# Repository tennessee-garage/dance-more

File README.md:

# dance-more
The next generation of the dancefloor

To get the repo running on your own machine (no floor needed), start with
[docs/getting-started.md](docs/getting-started.md).

Design docs live in [docs/](docs/README.md). To write an animation for the floor, start with [docs/animations.md](docs/animations.md).

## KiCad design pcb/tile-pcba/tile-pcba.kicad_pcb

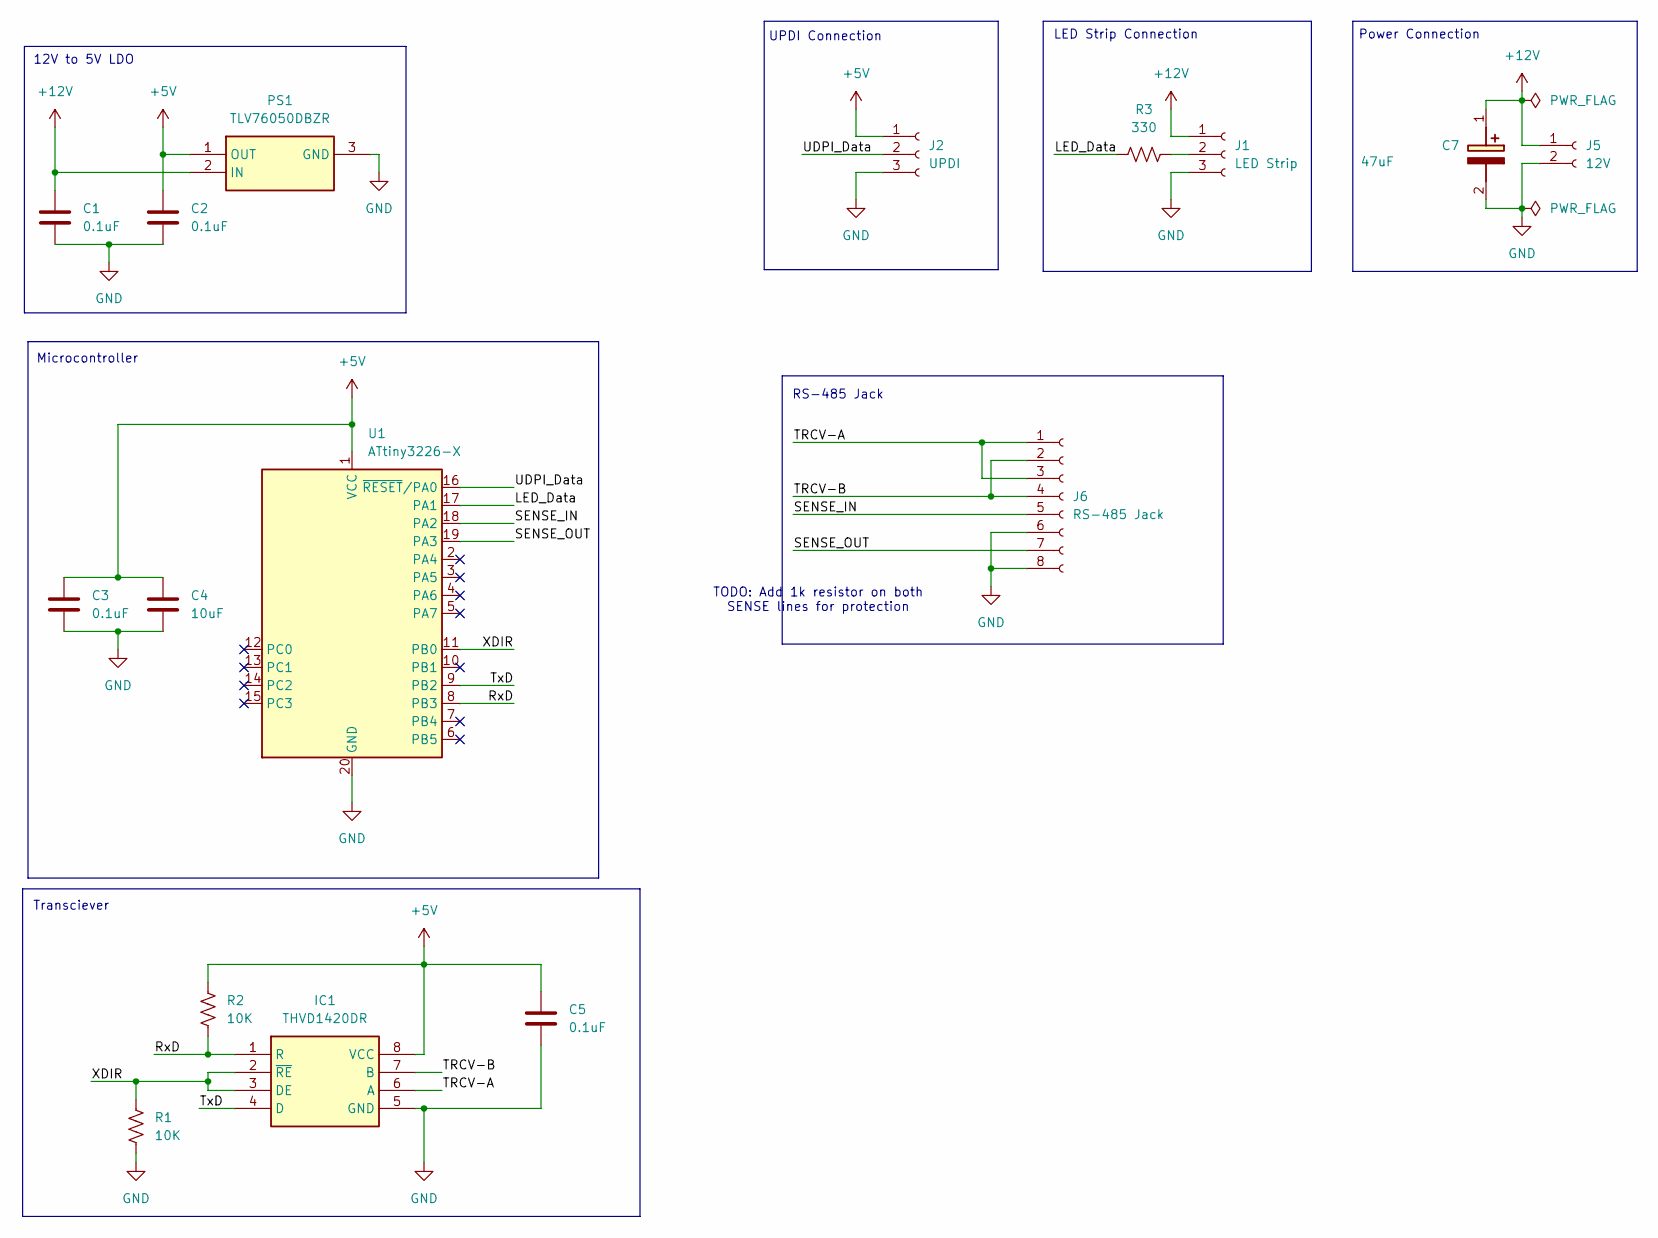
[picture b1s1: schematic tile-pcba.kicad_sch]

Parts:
C1, C2, C3, C5: 0.1uF; C_0805_2012Metric_Pad1.18x1.45mm_HandSolder; LCSC C49678
C4: 10uF; C_0805_2012Metric_Pad1.18x1.45mm_HandSolder; LCSC C1713
C7: 47uF; CAPAE530X550N; Mouser Part Number 710-865080342006
IC1: THVD1420DR; SOIC127P600X175-8N; Mouser Part Number 595-THVD1420DR
J1: LED Strip; PinHeader_1x03_P2.54mm_Vertical; LCSC C92159
J2: UPDI; PinHeader_1x03_P2.54mm_Vertical
J5: 12V; JST_XH_B2B-XH-A_1x02_P2.50mm_Vertical; LCSC C158012
J6: RS-485 Jack; 8P8C RA RJ45 Jack
PS1: TLV76050DBZR; SOT95P237X112-3N; Mouser Part Number 595-TLV76050DBZR
R1, R2: 10K; R_0805_2012Metric_Pad1.20x1.40mm_HandSolder; LCSC C17414
R3: 330; R_0805_2012Metric_Pad1.20x1.40mm_HandSolder; LCSC C17630
U1: ATtiny3226-X; SSOP-20_5.3x7.2mm_P0.65mm; Manufacturer Part Number ATTINY3226-XF; Mouser Part Number 579-ATTINY3226-XF

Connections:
+5V: C2.1, C3.1, C4.1, C5.1, IC1.8 (VCC), J2.1, PS1.1 (OUT), R2.1, U1.1 (VCC)
+12V: C1.1, C7.1 (+), J1.1, J5.1, PS1.2 (IN)
/LED_Data: R3.1, U1.17 (PA1)
/RxD: IC1.1 (R), R2.2, U1.8 (PB3)
/SENSE_IN: J6.5, U1.18 (PA2)
/SENSE_OUT: J6.7, U1.19 (PA3)
/TRCV-A: IC1.6 (A), J6.1, J6.3
/TRCV-B: IC1.7 (B), J6.2, J6.4
/TxD: IC1.4 (D), U1.9 (PB2)
/UDPI_Data: J2.2, U1.16 (~RESET/PA0)
/XDIR: IC1.2 (~RE), IC1.3 (DE), R1.1, U1.11 (PB0)
GND: C1.2, C2.2, C3.2, C4.2, C5.2, C7.2 (-), IC1.5 (GND), J1.3, J2.3, J5.2, J6.6, J6.8, PS1.3 (GND), R1.2, U1.20 (GND)
unnamed: J1.2, R3.2

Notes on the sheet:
TODO: Add 1k resistor on both SENSE lines for protection
UPDI Connection
LED Strip Connection
RS-485 Jack
Microcontroller
12V to 5V LDO
Transciever
Power Connection

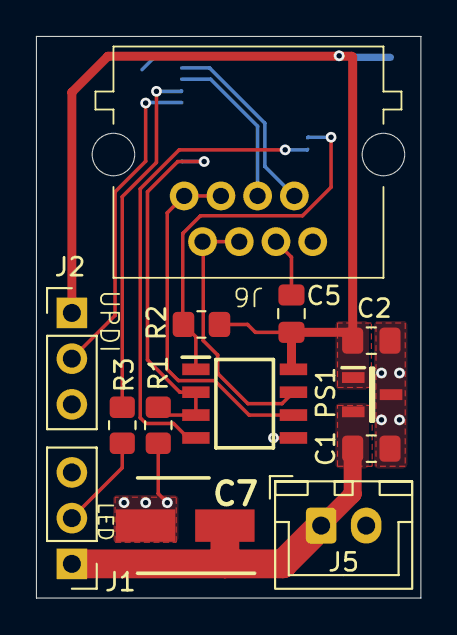
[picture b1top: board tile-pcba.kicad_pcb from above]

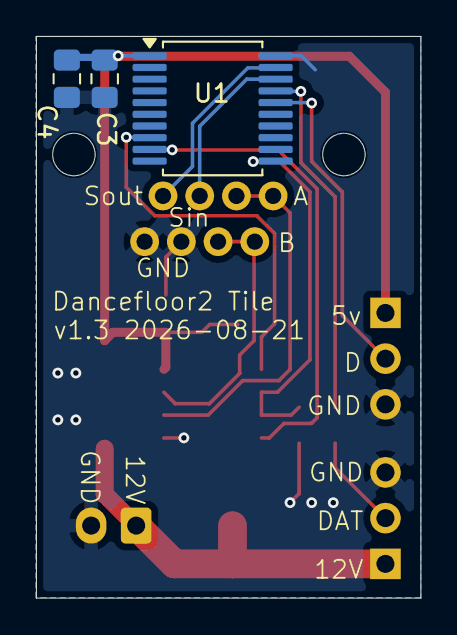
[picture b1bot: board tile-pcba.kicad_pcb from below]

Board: 2 copper layers, 21.4 x 31.2 mm, 16 parts (3 on the bottom side), 13 nets.

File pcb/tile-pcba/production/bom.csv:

Designator,Footprint,Quantity,Value,LCSC Part #
"C1, C2, C3, C5",0805,4,0.1uF,C49678
C4,0805,1,10uF,C1713
C7,CAPAE530X550N,1,47uF,C249915
IC1,SOIC127P600X175-8N,1,THVD1420DR,C3235215
J1,PinHeader_1x03_P2.54mm_Vertical,1,LED Strip,C92159
J2,PinHeader_1x03_P2.54mm_Vertical,1,UPDI,
J5,JST_XH_B2B-XH-A_1x02_P2.50mm_Vertical,1,12V,C158012
J6,8P8C RA RJ45 Jack,1,RS-485 Jack,
PS1,SOT95P237X112-3N,1,TLV76050DBZR,C2867465
"R1, R2",0805,2,10K,C17414
R3,0805,1,330,C17630
U1,SSOP-20_5.3x7.2mm_P0.65mm,1,ATtiny3226-X,C3235640

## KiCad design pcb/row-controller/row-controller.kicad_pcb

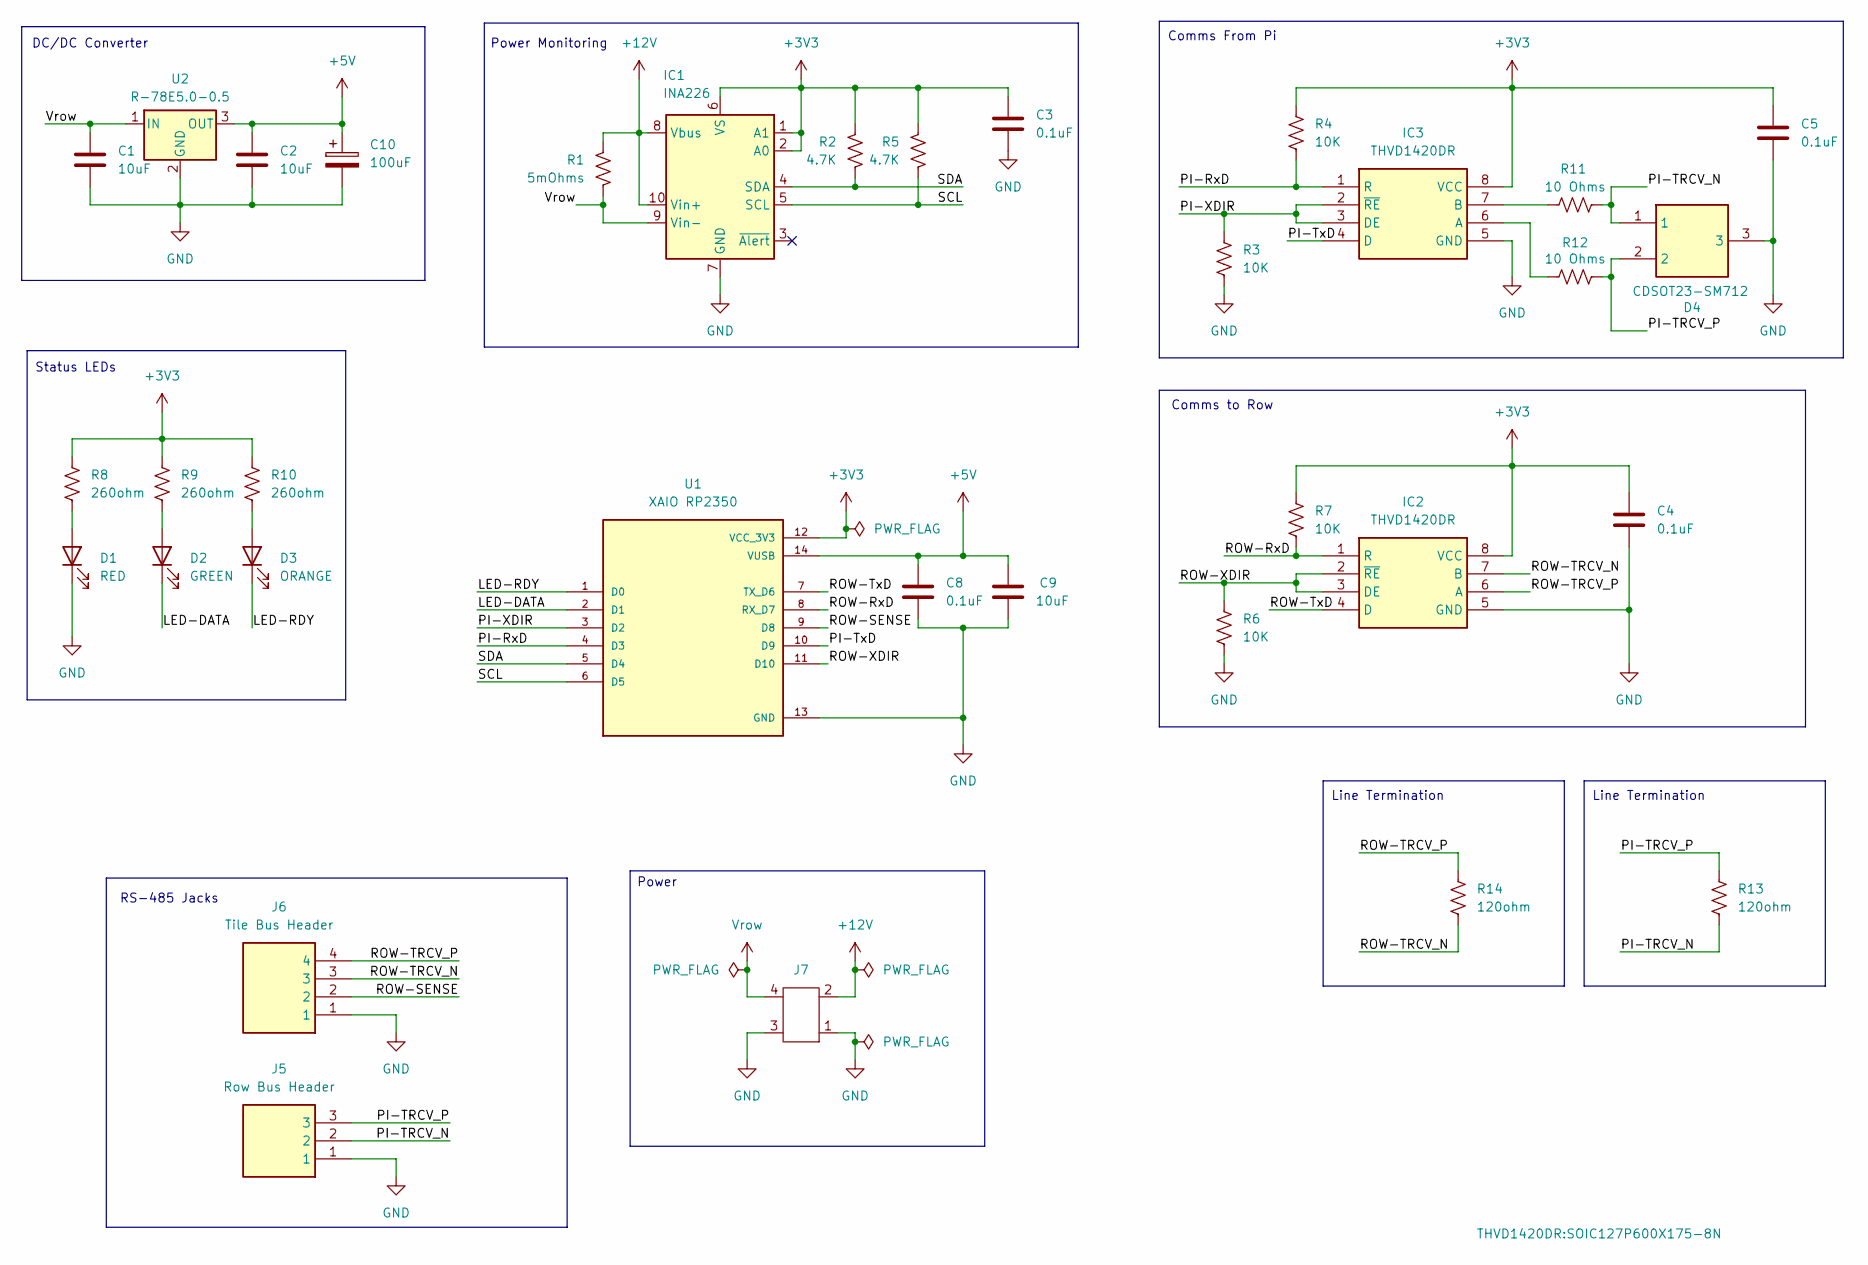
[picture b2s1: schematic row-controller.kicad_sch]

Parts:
C1, C2, C9: 10uF; C_0805_2012Metric_Pad1.18x1.45mm_HandSolder
C3, C4, C5, C8: 0.1uF; C_0805_2012Metric_Pad1.18x1.45mm_HandSolder
C10: 100uF; CP_Radial_D5.0mm_P2.00mm
D1: RED; LED_0805_2012Metric_Pad1.15x1.40mm_HandSolder
D2: GREEN; LED_0805_2012Metric_Pad1.15x1.40mm_HandSolder
D3: ORANGE; LED_0805_2012Metric_Pad1.15x1.40mm_HandSolder
D4: CDSOT23-SM712; SOT95P230X117-3N; Mouser Part Number 652-CDSOT23-SM712
IC1: INA226; TSSOP-10_3x3mm_P0.5mm; Mouser Part Number 595-INA220BIDGSR
IC2, IC3: THVD1420DR; SOIC127P600X175-8N; Mouser Part Number 595-THVD1420DR
J5: Row Bus Header; 1548129; Mouser Part Number 651-1548129
J6: Tile Bus Header; TB003-500-P04BE; Mouser Part Number 490-TB003-500-P04BE
J7: Quad Powerpole
R1: 5mOhms; R_2010_5025Metric_Pad1.40x2.65mm_HandSolder; Manufacturer Part Number LRMAT2010-R005FT4; Mouser Part Number 756-LRMAT2010R005FT4
R2, R5: 4.7K; R_0805_2012Metric_Pad1.20x1.40mm_HandSolder
R3, R4, R6, R7: 10K; R_0805_2012Metric_Pad1.20x1.40mm_HandSolder
R8, R9, R10: 260ohm; R_0805_2012Metric_Pad1.20x1.40mm_HandSolder
R11: 10 Ohms; R_1206_3216Metric_Pad1.30x1.75mm_HandSolder; Manufacturer Part Number CRCW120610R0FKEAHP; Mouser Part Number 71-CRCW120610R0FKEAH
R12: 10 Ohms; R_1206_3216Metric_Pad1.30x1.75mm_HandSolder
R13, R14: 120ohm; R_0805_2012Metric_Pad1.20x1.40mm_HandSolder
U1: XAIO RP2350; MODULE_113991054; PARTREV 23/05/2022; Mouser Part Number 713-102010550
U2: R-78E5.0-0.5; Converter_DCDC_RECOM_R-78E-0.5_THT; Manufacturer Part Number R-78E5.0-0.5; Mouser Part Number 919-R-78E5.0-0.5

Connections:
+3V3: C3.1, C4.1, C5.1, IC1.1 (A1), IC1.2 (A0), IC1.6 (VS), IC2.8 (VCC), IC3.8 (VCC), R2.1, R4.1, R5.1, R7.1, R8.1, R9.1, R10.1, U1.12 (VCC_3V3)
+5V: C2.1, C8.1, C9.1, C10.1, U1.14 (VUSB), U2.3 (OUT)
+12V: IC1.8 (Vbus), IC1.10 (Vin+), J7.2, R1.1
/LED-DATA: D2.1 (K), U1.2 (D1)
/LED-RDY: D3.1 (K), U1.1 (D0)
/PI-RxD: IC3.1 (R), R4.2, U1.4 (D3)
/PI-TRCV_N: D4.1, J5.2, R11.2, R13.2
/PI-TRCV_P: D4.2, J5.3, R12.2, R13.1
/PI-TxD: IC3.4 (D), U1.10 (D9)
/PI-XDIR: IC3.2 (~RE), IC3.3 (DE), R3.1, U1.3 (D2)
/ROW-RxD: IC2.1 (R), R7.2, U1.8 (RX_D7)
/ROW-SENSE: J6.2, U1.9 (D8)
/ROW-TRCV_N: IC2.7 (B), J6.3, R14.2
/ROW-TRCV_P: IC2.6 (A), J6.4, R14.1
/ROW-TxD: IC2.4 (D), U1.7 (TX_D6)
/ROW-XDIR: IC2.2 (~RE), IC2.3 (DE), R6.1, U1.11 (D10)
/SCL: IC1.5 (SCL), R5.2, U1.6 (D5)
/SDA: IC1.4 (SDA), R2.2, U1.5 (D4)
GND: C1.2, C2.2, C3.2, C4.2, C5.2, C8.2, C9.2, C10.2, D1.1 (K), D4.3, IC1.7 (GND), IC2.5 (GND), IC3.5 (GND), J5.1, J6.1, J7.1, J7.3, R3.2, R6.2, U1.13 (GND), U2.2 (GND)
unnamed: D1.2 (A), R8.2
unnamed: D2.2 (A), R9.2
unnamed: D3.2 (A), R10.2
unnamed: IC3.6 (A), R12.1
unnamed: IC3.7 (B), R11.1
Vrow: C1.1, IC1.9 (Vin-), J7.4, R1.2, U2.1 (IN)

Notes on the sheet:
Power Monitoring
Line Termination
Power
Comms to Row
Status LEDs
Comms From Pi
DC/DC Converter
RS-485 Jacks

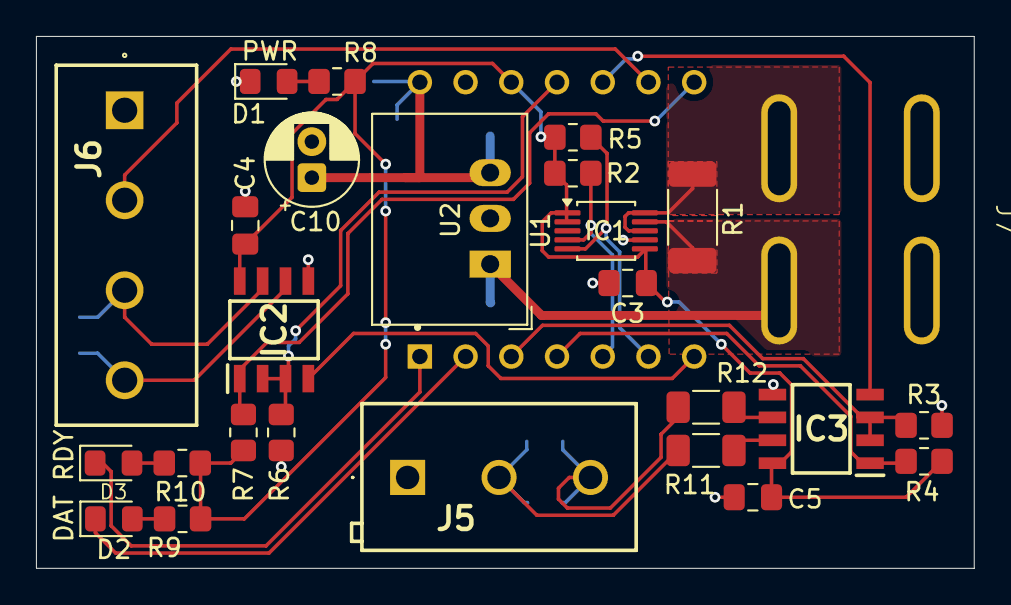
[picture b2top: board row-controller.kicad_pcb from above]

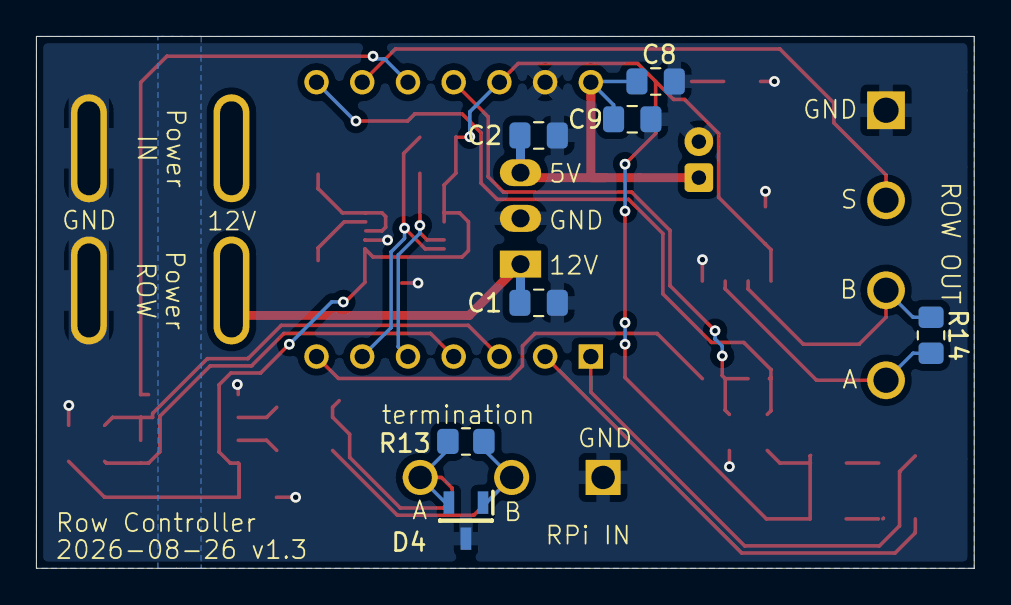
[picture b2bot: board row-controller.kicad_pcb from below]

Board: 2 copper layers, 52.1 x 29.5 mm, 34 parts (7 on the bottom side), 25 nets.

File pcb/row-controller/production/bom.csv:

Designator,Footprint,Quantity,Value,LCSC Part #
"C1, C2, C9",0805,3,10uF,
C10,CP_Radial_D5.0mm_P2.00mm,1,100uF,
"C3, C4, C5, C8",0805,4,0.1uF,
D1,0805,1,RED,
D2,0805,1,GREEN,
D3,0805,1,ORANGE,
D4,SOT95P230X117-3N,1,CDSOT23-SM712,
IC1,TSSOP-10_3x3mm_P0.5mm,1,INA226,
"IC2, IC3",SOIC127P600X175-8N,2,THVD1420DR,
J5,1548129,1,Row Bus Header,
J6,TB003-500-P04BE,1,Tile Bus Header,
J7,Quad Powerpole,1,~,
R1,2010,1,5mOhms,
"R10, R8, R9",0805,3,260ohm,
"R11, R12",1206,2,10 Ohms,
"R13, R14",0805,2,120ohm,
"R2, R5",0805,2,4.7K,
"R3, R4, R6, R7",0805,4,10K,
U1,MODULE_113991054,1,XAIO RP2350,
U2,Converter_DCDC_RECOM_R-78E-0.5_THT,1,R-78E5.0-0.5,

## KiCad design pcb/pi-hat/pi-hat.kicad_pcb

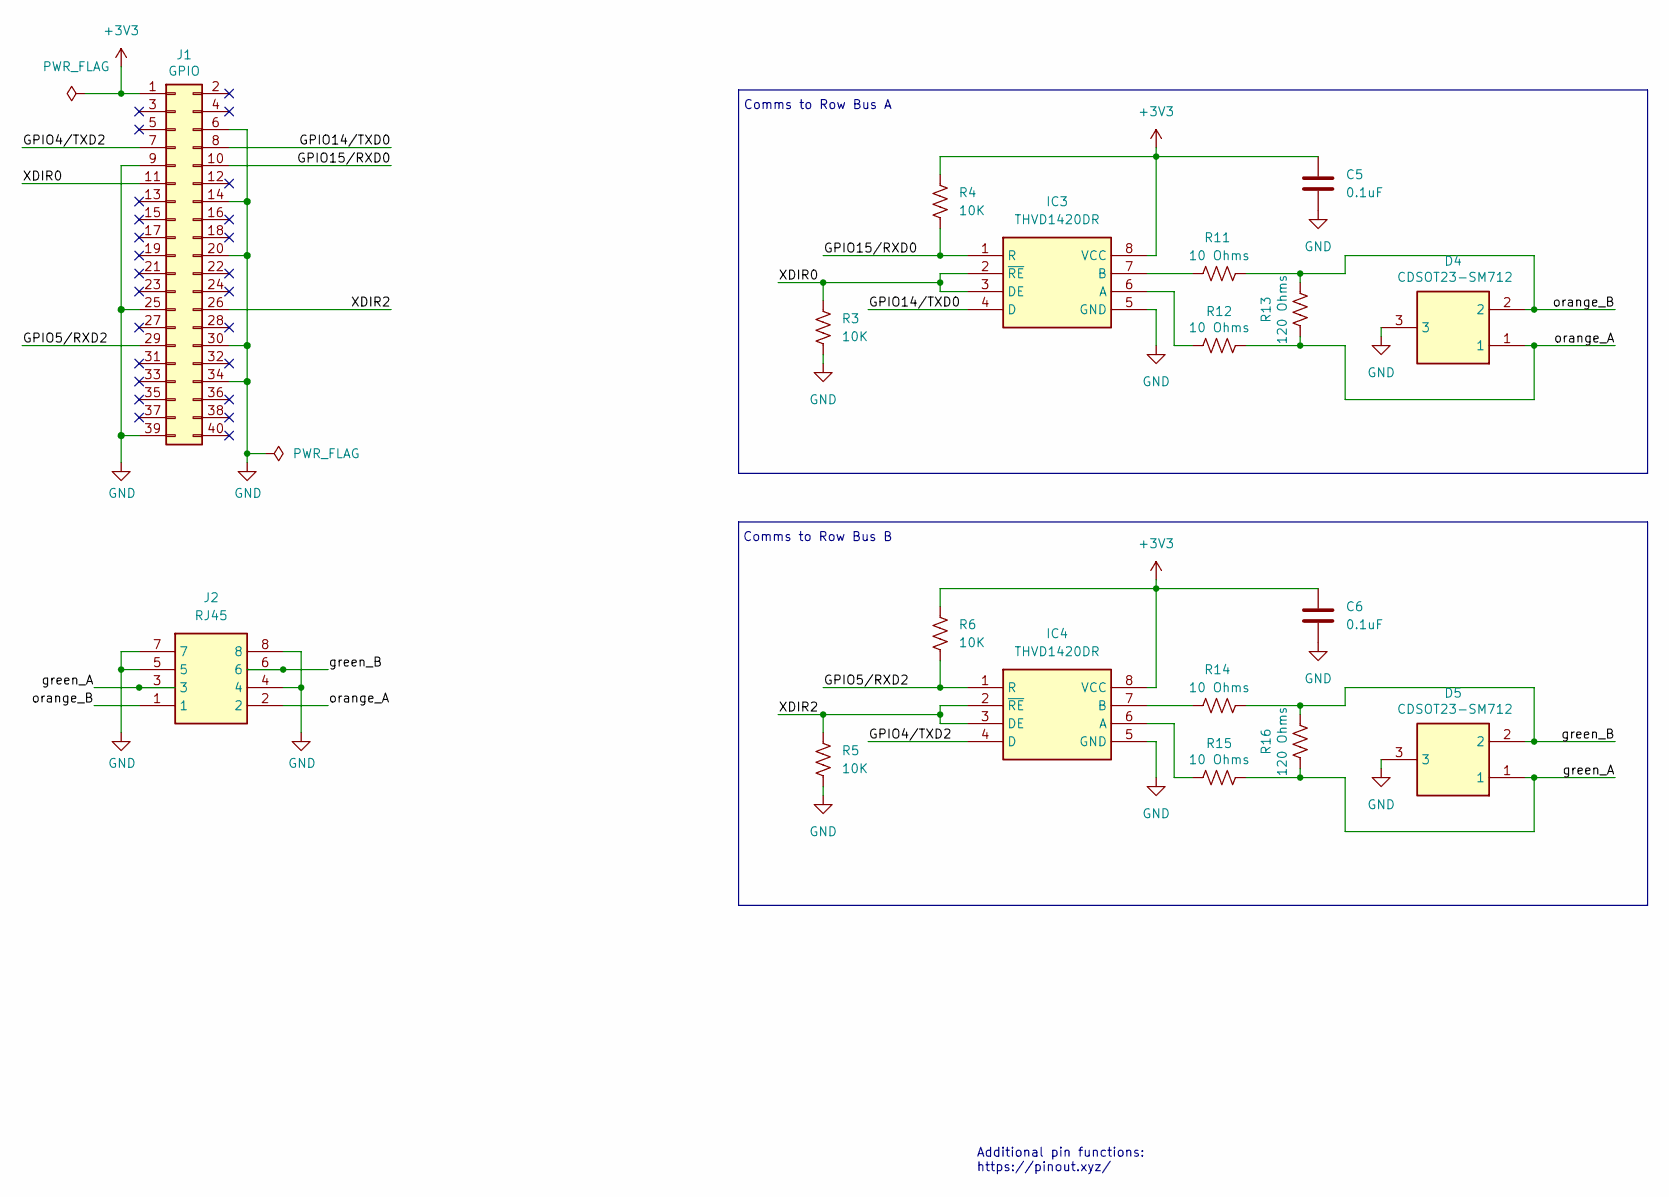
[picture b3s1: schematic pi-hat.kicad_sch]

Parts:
C5, C6: 0.1uF; C_0805_2012Metric_Pad1.18x1.45mm_HandSolder
D4, D5: CDSOT23-SM712; SOT95P230X117-3N; Mouser Part Number 652-CDSOT23-SM712
IC3, IC4: THVD1420DR; SOIC127P600X175-8N; Mouser Part Number 595-THVD1420DR
J1: GPIO; PinSocket_2x20_P2.54mm_Vertical
J2: RJ45; MJ3225880; Mouser Part Number 640-MJ3225880
R3, R4, R5, R6: 10K; R_0805_2012Metric_Pad1.20x1.40mm_HandSolder
R11, R12, R14, R15: 10 Ohms; R_1206_3216Metric_Pad1.30x1.75mm_HandSolder
R13, R16: 120 Ohms; R_0805_2012Metric_Pad1.20x1.40mm_HandSolder

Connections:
+3V3: C5.1, C6.1, IC3.8 (VCC), IC4.8 (VCC), J1.1, R4.1, R6.1
/GPIO4/TXD2: IC4.4 (D), J1.7
/GPIO5/RXD2: IC4.1 (R), J1.29, R6.2
/GPIO14/TXD0: IC3.4 (D), J1.8
/GPIO15/RXD0: IC3.1 (R), J1.10, R4.2
/XDIR0: IC3.2 (~RE), IC3.3 (DE), J1.11, R3.1
/XDIR2: IC4.2 (~RE), IC4.3 (DE), J1.26, R5.1
/green_A: D5.1, J2.3, R15.2, R16.1
/green_B: D5.2, J2.6, R14.2, R16.2
/orange_A: D4.1, J2.2, R12.2, R13.1
/orange_B: D4.2, J2.1, R11.2, R13.2
GND: C5.2, C6.2, D4.3, D5.3, IC3.5 (GND), IC4.5 (GND), J1.6, J1.9, J1.14, J1.20, J1.25, J1.30, J1.34, J1.39, J2.4, J2.5, J2.7, J2.8, R3.2, R5.2
unnamed: IC3.6 (A), R12.1
unnamed: IC3.7 (B), R11.1
unnamed: IC4.6 (A), R15.1
unnamed: IC4.7 (B), R14.1

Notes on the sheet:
Comms to Row Bus B
Additional pin functions: https://pinout.xyz/
Comms to Row Bus A

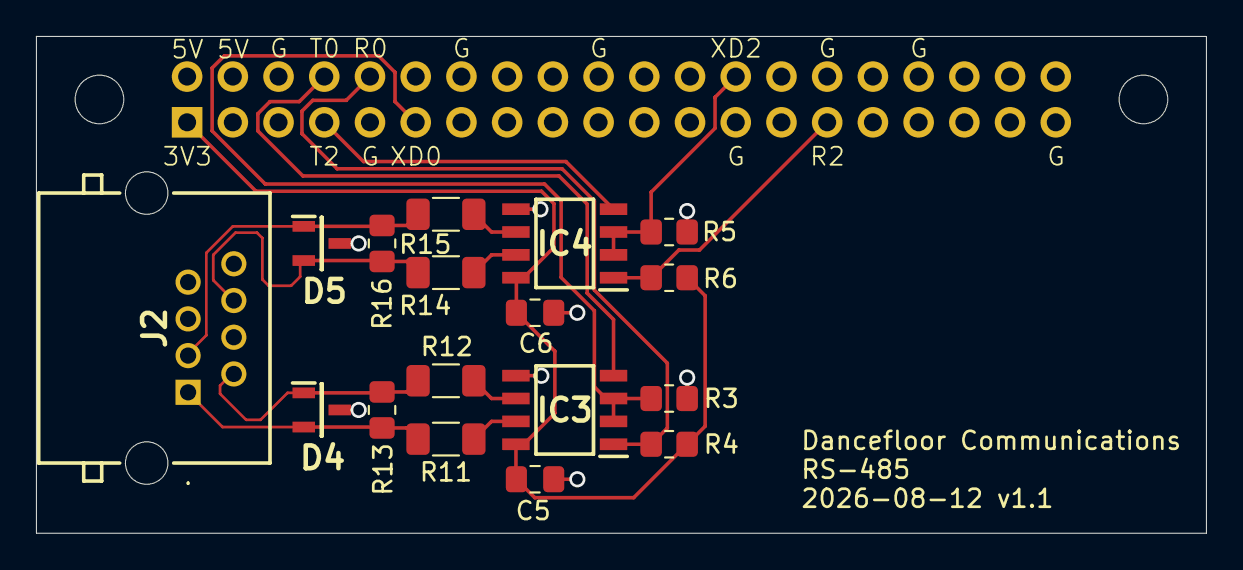
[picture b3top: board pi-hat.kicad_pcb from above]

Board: 2 copper layers, 65.0 x 27.6 mm, 20 parts (1 on the bottom side), 16 nets.

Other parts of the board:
MH1, MH2: MountingHole_2.7mm_M2.5

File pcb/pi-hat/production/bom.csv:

Designator,Footprint,Quantity,Value,LCSC Part #
"C5, C6",0805,2,0.1uF,
"D4, D5",SOT95P230X117-3N,2,CDSOT23-SM712,
"IC3, IC4",SOIC127P600X175-8N,2,THVD1420DR,
J1,PinSocket_2x20_P2.54mm_Vertical,1,GPIO,
J2,MJ3225880,1,RJ45,
"R11, R12, R14, R15",1206,4,10 Ohms,
"R13, R16",0805,2,120 Ohms,
"R3, R4, R5, R6",0805,4,10K,

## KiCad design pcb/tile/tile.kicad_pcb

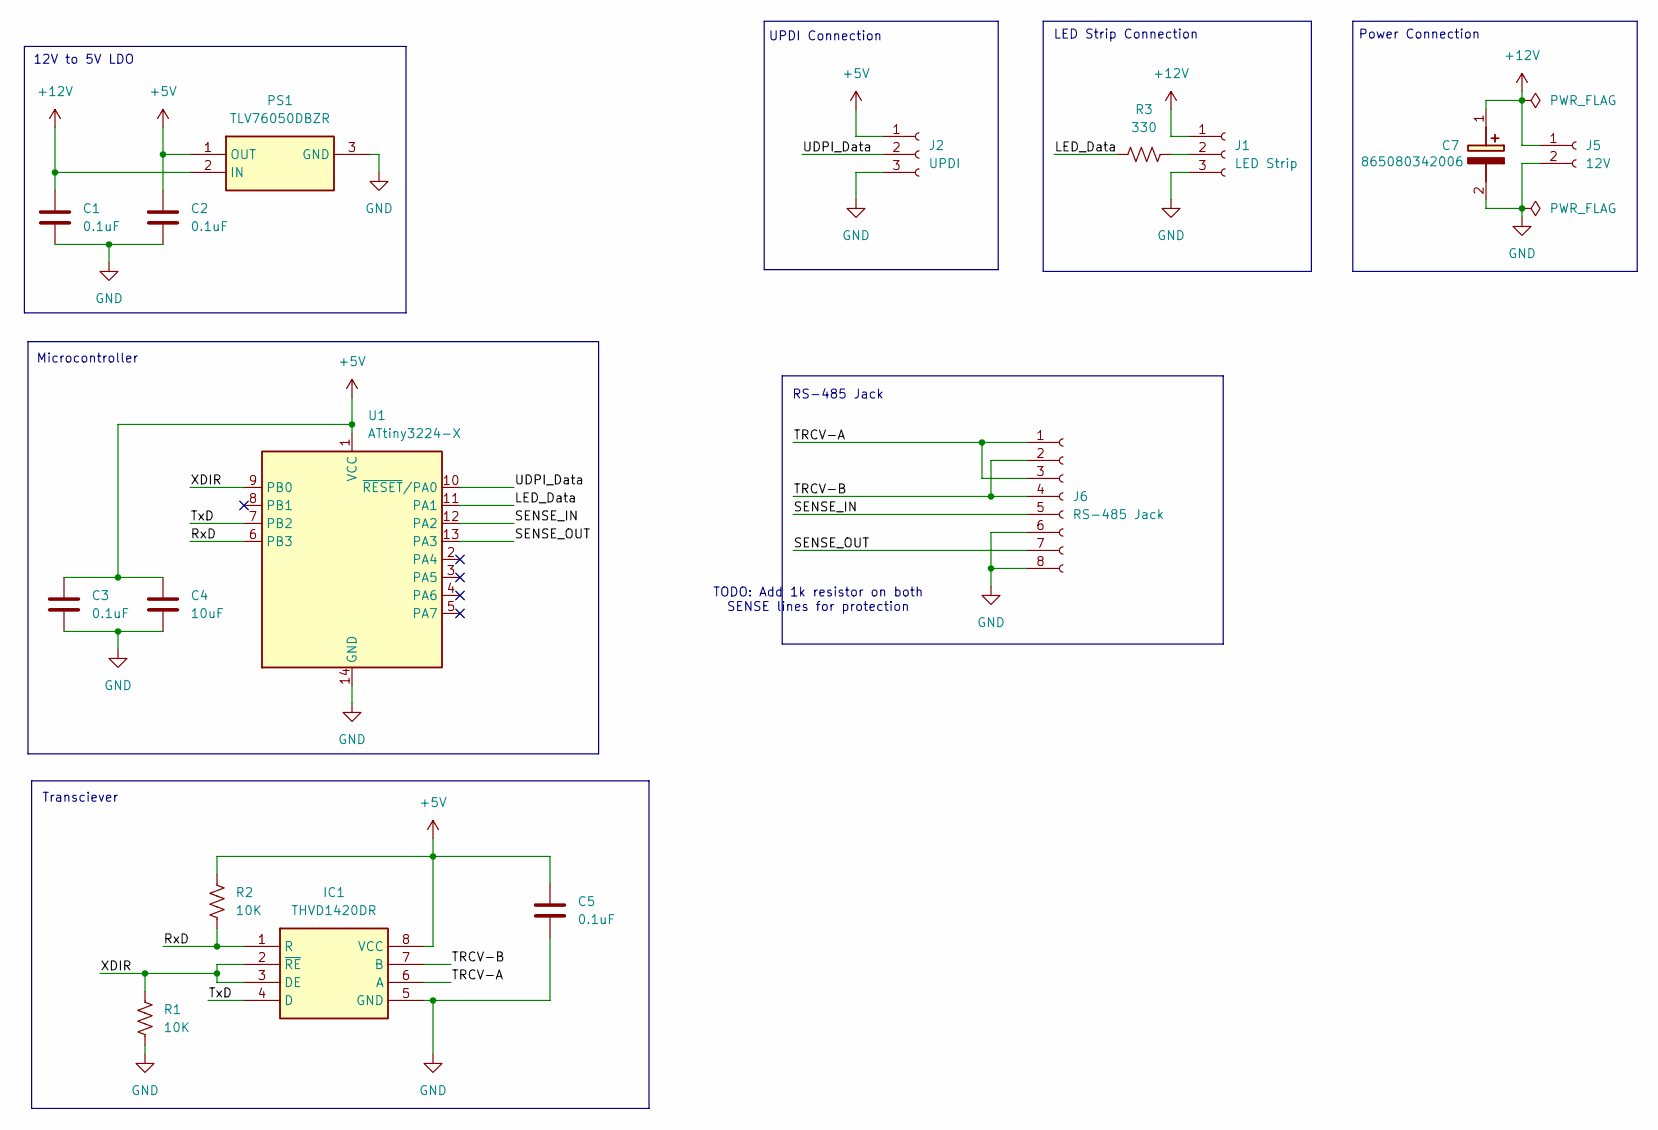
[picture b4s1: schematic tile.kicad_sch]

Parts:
C1, C2, C3, C5: 0.1uF; C_0805_2012Metric_Pad1.18x1.45mm_HandSolder
C4: 10uF; C_0805_2012Metric_Pad1.18x1.45mm_HandSolder
C7: 865080342006; CAPAE530X550N; Mouser Part Number 710-865080342006
IC1: THVD1420DR; SOIC127P600X175-8N; Mouser Part Number 595-THVD1420DR
J1: LED Strip; PinHeader_1x03_P2.54mm_Vertical
J2: UPDI; PinHeader_1x03_P2.54mm_Vertical
J5: 12V; JST_XH_B2B-XH-A_1x02_P2.50mm_Vertical
J6: RS-485 Jack; 6P6C RA RJ45 Jack
PS1: TLV76050DBZR; SOT95P237X112-3N; Mouser Part Number 595-TLV76050DBZR
R1, R2: 10K; R_0805_2012Metric_Pad1.20x1.40mm_HandSolder
R3: 330; R_0805_2012Metric_Pad1.20x1.40mm_HandSolder
U1: ATtiny3224-X; TSSOP-14_4.4x5mm_P0.65mm; Manufacturer Part Number ATTINY3224-XF; Mouser Part Number 579-ATTINY3224-XF

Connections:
+5V: C2.1, C3.1, C4.1, C5.1, IC1.8 (VCC), J2.1, PS1.1 (OUT), R2.1, U1.1 (VCC)
+12V: C1.1, C7.1 (+), J1.1, J5.1, PS1.2 (IN)
/LED_Data: R3.1, U1.11 (PA1)
/RxD: IC1.1 (R), R2.2, U1.6 (PB3)
/SENSE_IN: J6.5, U1.12 (PA2)
/SENSE_OUT: J6.7, U1.13 (PA3)
/TRCV-A: IC1.6 (A), J6.1, J6.3
/TRCV-B: IC1.7 (B), J6.2, J6.4
/TxD: IC1.4 (D), U1.7 (PB2)
/UDPI_Data: J2.2, U1.10 (~RESET/PA0)
/XDIR: IC1.2 (~RE), IC1.3 (DE), R1.1, U1.9 (PB0)
GND: C1.2, C2.2, C3.2, C4.2, C5.2, C7.2 (-), IC1.5 (GND), J1.3, J2.3, J5.2, J6.6, J6.8, PS1.3 (GND), R1.2, U1.14 (GND)
unnamed: J1.2, R3.2

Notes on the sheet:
TODO: Add 1k resistor on both SENSE lines for protection
UPDI Connection
LED Strip Connection
RS-485 Jack
Microcontroller
12V to 5V LDO
Transciever
Power Connection

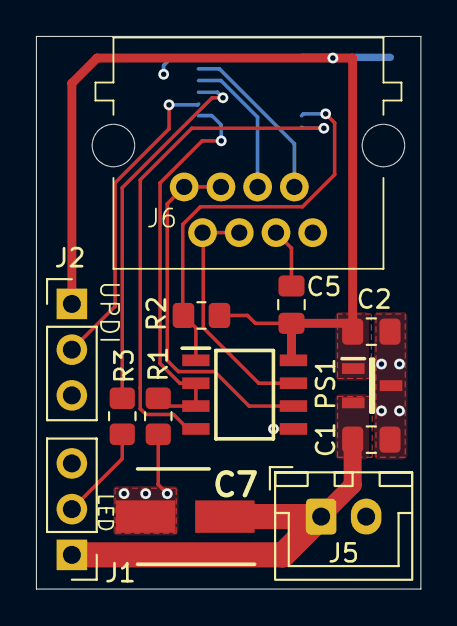
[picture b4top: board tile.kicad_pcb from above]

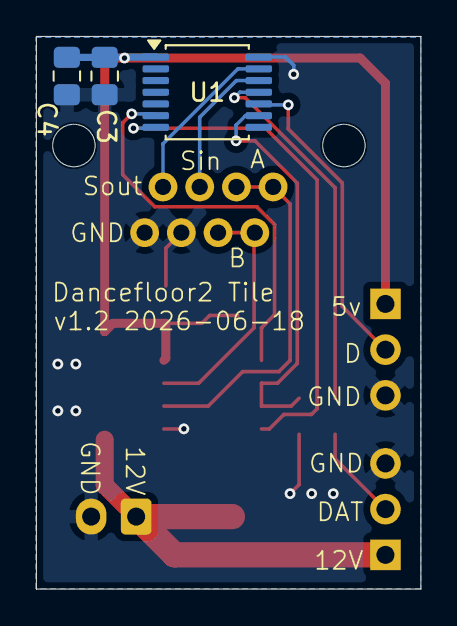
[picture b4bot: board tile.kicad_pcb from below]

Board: 2 copper layers, 21.4 x 30.7 mm, 16 parts (3 on the bottom side), 13 nets.

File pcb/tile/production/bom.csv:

Designator,Footprint,Quantity,Value,LCSC Part #
"C1, C2, C3, C5",0805,4,0.1uF,
C4,0805,1,10uF,
C7,CAPAE530X550N,1,47uF,
IC1,SOIC127P600X175-8N,1,THVD1420DR,
J1,PinHeader_1x03_P2.54mm_Vertical,1,LED Strip,
J2,PinHeader_1x03_P2.54mm_Vertical,1,UPDI,
J5,JST_XH_B2B-XH-A_1x02_P2.50mm_Vertical,1,12V,
J6,8P8C RA RJ45 Jack,1,RS-485 Jack,
PS1,SOT95P237X112-3N,1,TLV76050DBZR,
"R1, R2",0805,2,10K,
R3,0805,1,330,
U1,TSSOP-14_4.4x5mm_P0.65mm,1,ATtiny3224-X,

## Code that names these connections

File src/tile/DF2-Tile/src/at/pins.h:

#pragma once
// Pin assignments for the ATtiny3224 tile board.
// These are tentative values from the issue spec — verify against
// pcb/tile/tile.kicad_sch and update before flashing hardware.

// WS2815 LED data line (800 KHz, GRB)
#define PIN_LED_DATA  PIN_PA1

// RS-485 direction control (THVD1420DR XDIR/DE)
// HIGH = TX (driver enabled), LOW = RX (default)
#define PIN_DE        PIN_PB0

// SENSE chain GPIO
// SENSE_IN:  driven LOW by the upstream node to signal this tile
// SENSE_OUT: driven LOW by this tile to signal the downstream node;
//            released by returning the pin to high-impedance input
#define PIN_SENSE_IN  PIN_PA2
#define PIN_SENSE_OUT PIN_PA3

// UART0 pin selection (ATtiny3224 datasheet Table 6-1, PORTMUX.USARTROUTEA).
// megaTinyCore maps USART0 pins via Serial.swap(n) before Serial.begin():
//   swap 0 (default): TX=PA1, RX=PA2
//   swap 1 (alt):     TX=PB2, RX=PB3
#define PIN_UART_TX   PIN_PB2
#define PIN_UART_RX   PIN_PB3

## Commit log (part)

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2025-10-22 First rev of the tile and row controller
2025-10-22 Small tweaks
2025-10-23 Updated version of the tile that only uses on RJ45 jack vs two RJ12 jacks
2025-11-07 Slight adjustments to some text on the board
2025-11-07 Removed the ferrite bead, updated power symbols.
    Not convinced I need the beads, can do some testing to confirm this when I have test boards
2026-02-24 save changes before merging branch
2026-02-28 Simulator for how the floor would look with different types of edge on lighting
2026-02-28 Get the text overlay working for the controls
2026-06-18 Committing PCB changes before swaping out some components
2026-06-18 Slightly widened the 12V trace between the power in and strip
2026-06-21 Row controller with two power jacks; in from main power, out for row power
    This is necessary to actually measure the power sent to the row
2026-06-21 Additon of second power jack, plus notes/todos for things that need updating
    Checkpointing here since this is what the last fab got and I want to be able to come back to it
2026-06-21 Commit the gerbers and some images of the current verions that have been sent to fab
2026-06-21 Add docs created for the setup of this project
